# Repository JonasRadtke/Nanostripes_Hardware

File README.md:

# Nanostripes Hardware

## Nanostripes Led Modul

Dies ist das Led Modul für die Nanostripes Connectoren.
Der Connector sowie das LED Modul ist den Nanoleaf Lines nachempfunden. Auf dem Controller läuft das Reverse Engineered Nanoleaf Lines Protokoll.

## Nanostripes Connector

Dies ist der Connector für die Nanostripes Led Module.
Der Connector sowie das LED Modul ist den Nanoleaf Lines nachempfunden. Auf dem Controller läuft das Reverse Engineered Nanoleaf Lines Protokoll.

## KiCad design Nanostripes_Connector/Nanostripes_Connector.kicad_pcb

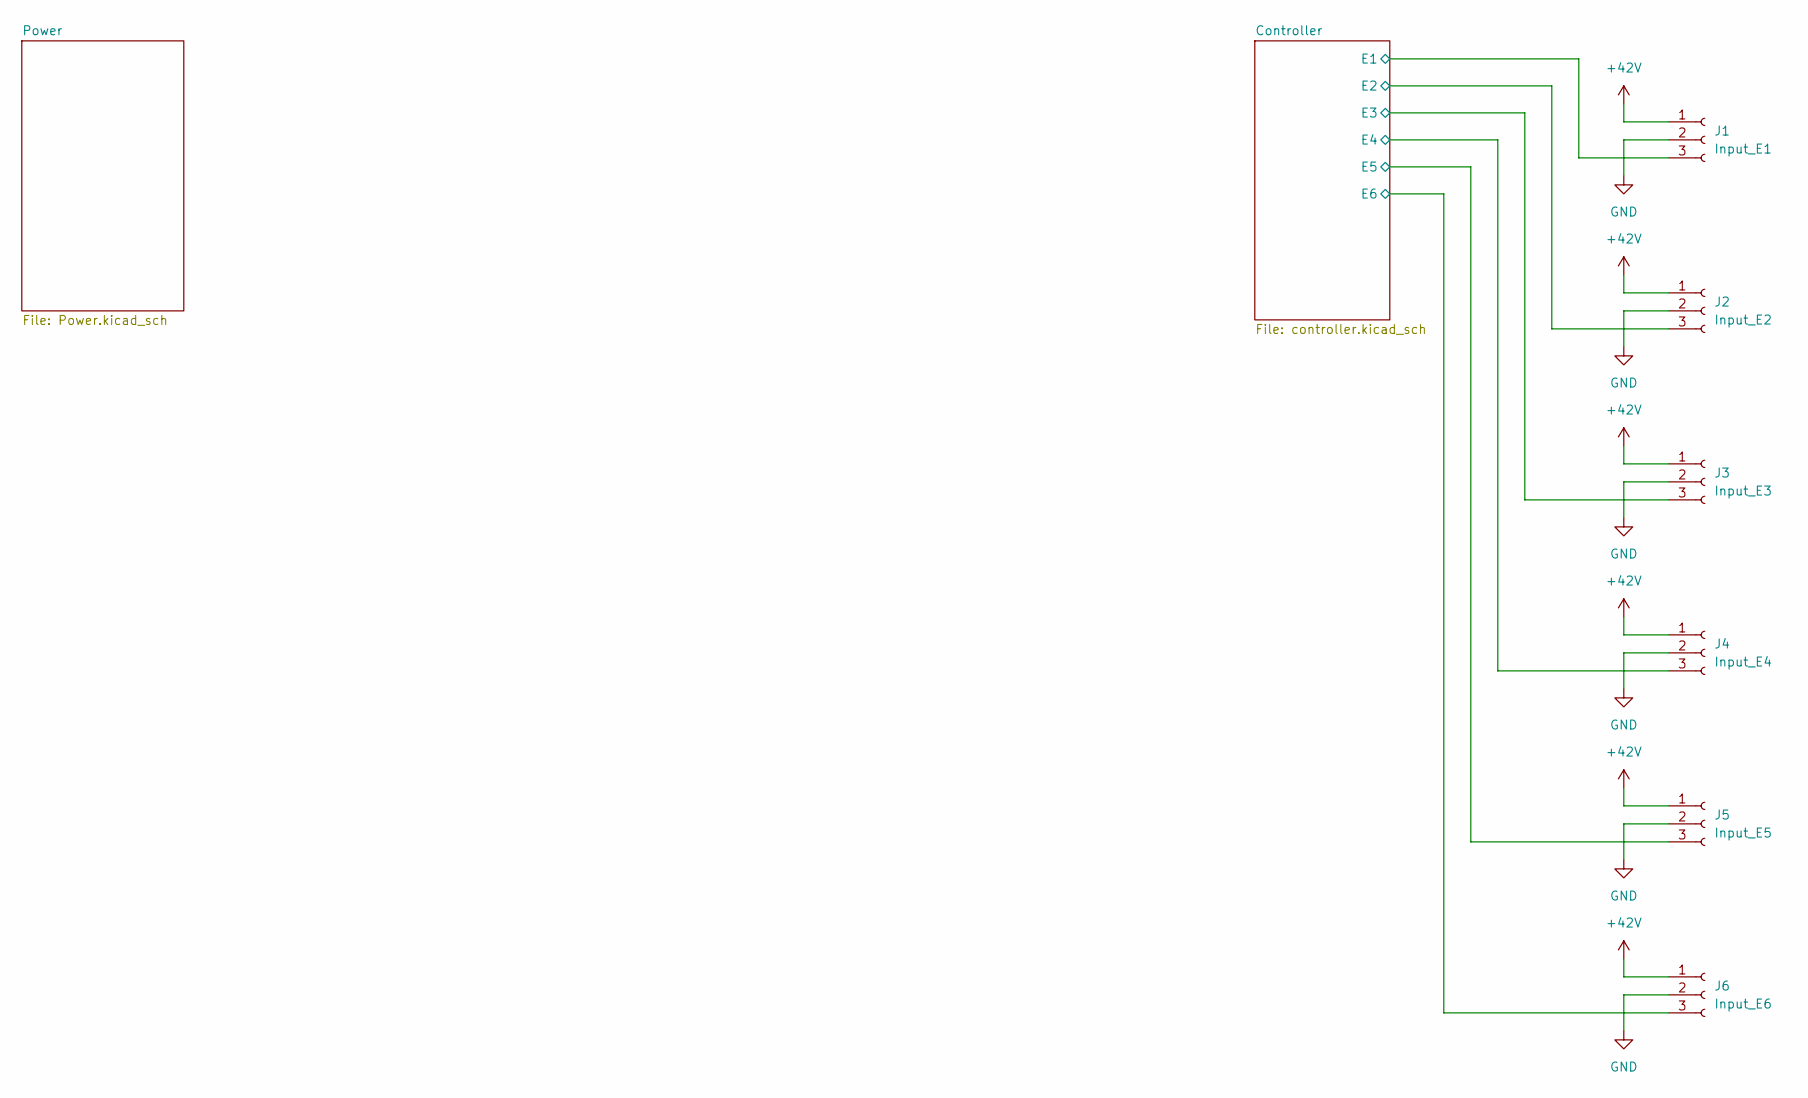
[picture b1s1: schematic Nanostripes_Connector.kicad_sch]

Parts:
J1: Input_E1; PinSocket_1x03_P2.54mm_Vertical
J2: Input_E2; PinSocket_1x03_P2.54mm_Vertical
J3: Input_E3; PinSocket_1x03_P2.54mm_Vertical
J4: Input_E4; PinSocket_1x03_P2.54mm_Vertical
J5: Input_E5; PinSocket_1x03_P2.54mm_Vertical
J6: Input_E6; PinSocket_1x03_P2.54mm_Vertical

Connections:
+42V: J1.1, J2.1, J3.1, J4.1, J5.1, J6.1; also elsewhere on the board
/Controller/E1: J1.3; also elsewhere on the board
/Controller/E2: J2.3; also elsewhere on the board
/Controller/E3: J3.3; also elsewhere on the board
/Controller/E4: J4.3; also elsewhere on the board
/Controller/E5: J5.3; also elsewhere on the board
/Controller/E6: J6.3; also elsewhere on the board
GND: J1.2, J2.2, J3.2, J4.2, J5.2, J6.2; also elsewhere on the board

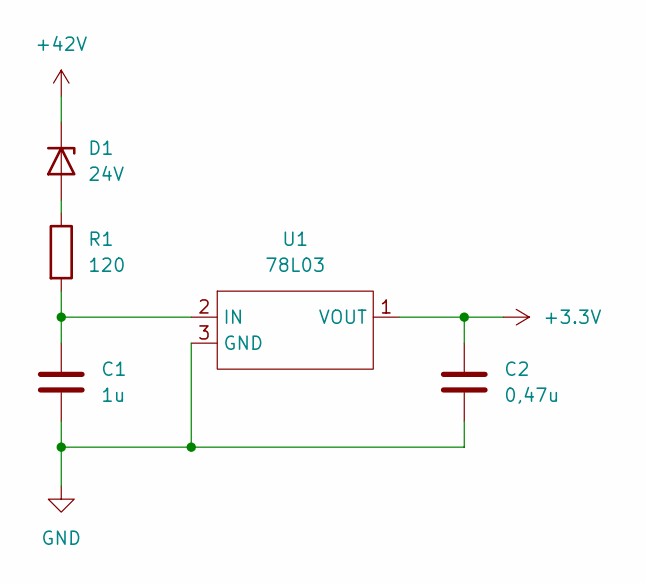
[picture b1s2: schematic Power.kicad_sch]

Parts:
C1: 1u; C_0805_2012Metric
C2: 0,47u; C_0805_2012Metric
D1: 24V; D_MiniMELF
R1: 120; R_0805_2012Metric
U1: 78L03; SOT-23-3

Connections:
+3.3V: C2.1, U1.1 (VOUT); also elsewhere on the board
+42V: D1.1 (K); also elsewhere on the board
GND: C1.2, C2.2, U1.3 (GND); also elsewhere on the board
unnamed: D1.2 (A), R1.1
unnamed: C1.1, R1.2, U1.2 (IN)

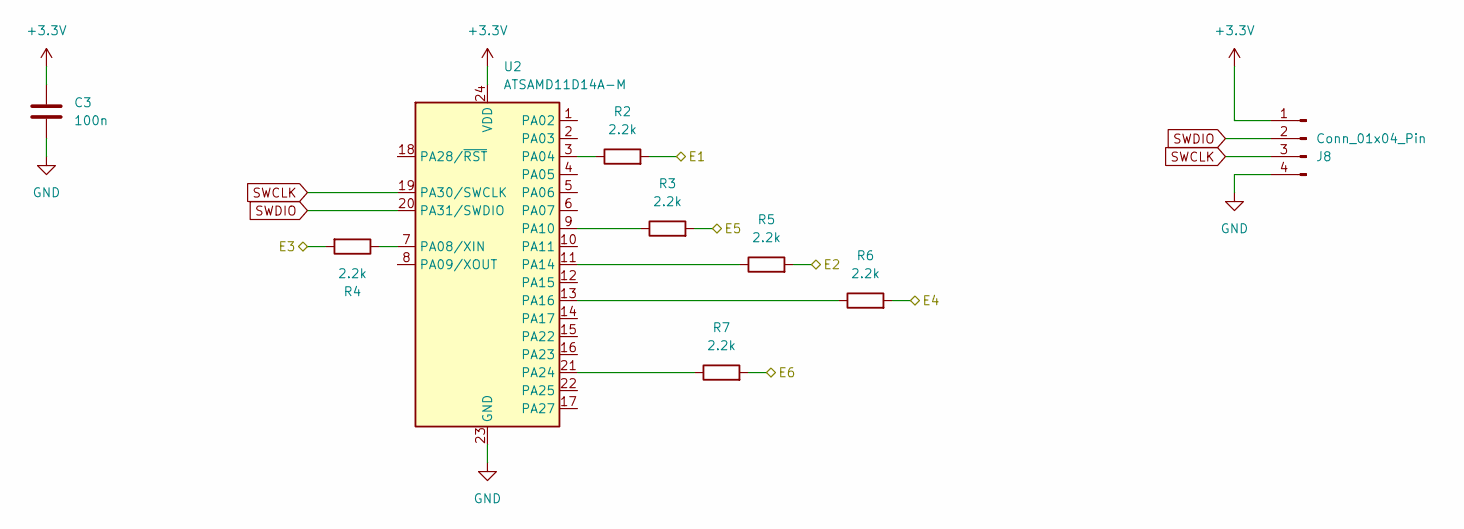
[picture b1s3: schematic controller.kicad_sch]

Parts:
C3: 100n; C_0805_2012Metric
J8: Conn_01x04_Pin; PinHeader_1x04_P2.54mm_Vertical
R2, R3, R4, R5, R6, R7: 2.2k; R_0805_2012Metric
U2: ATSAMD11D14A-M; QFN-24-1EP_4x4mm_P0.5mm_EP2.6x2.6mm

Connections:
+3.3V: C3.1, J8.1, U2.24 (VDD); also elsewhere on the board
/Controller/E1: R2.2; also elsewhere on the board
/Controller/E2: R5.2; also elsewhere on the board
/Controller/E3: R4.2; also elsewhere on the board
/Controller/E4: R6.2; also elsewhere on the board
/Controller/E5: R3.2; also elsewhere on the board
/Controller/E6: R7.2; also elsewhere on the board
GND: C3.2, J8.4, U2.23 (GND); also elsewhere on the board
unnamed: R2.1, U2.3 (PA04)
unnamed: R4.1, U2.7 (PA08/XIN)
unnamed: R3.1, U2.9 (PA10)
unnamed: R5.1, U2.11 (PA14)
unnamed: R6.1, U2.13 (PA16)
unnamed: R7.1, U2.21 (PA24)
SWCLK: J8.3, U2.19 (PA30/SWCLK)
SWDIO: J8.2, U2.20 (PA31/SWDIO)

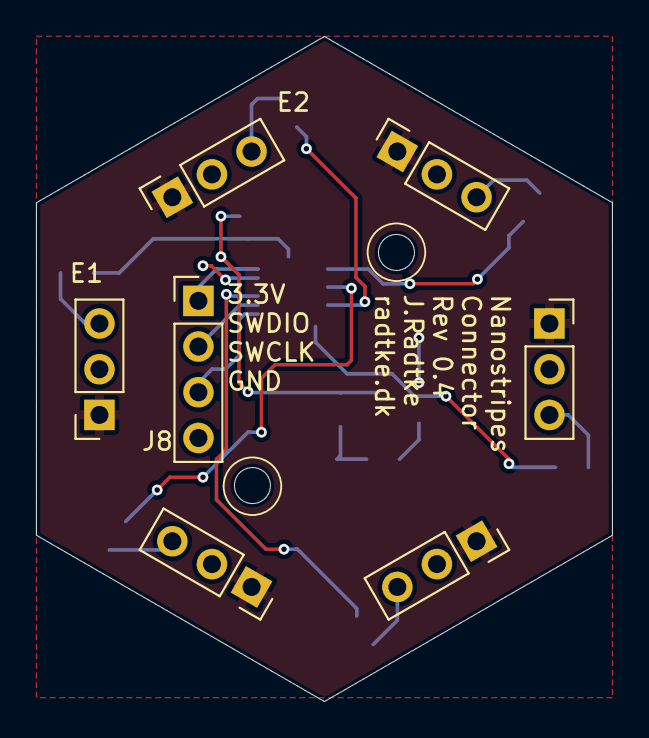
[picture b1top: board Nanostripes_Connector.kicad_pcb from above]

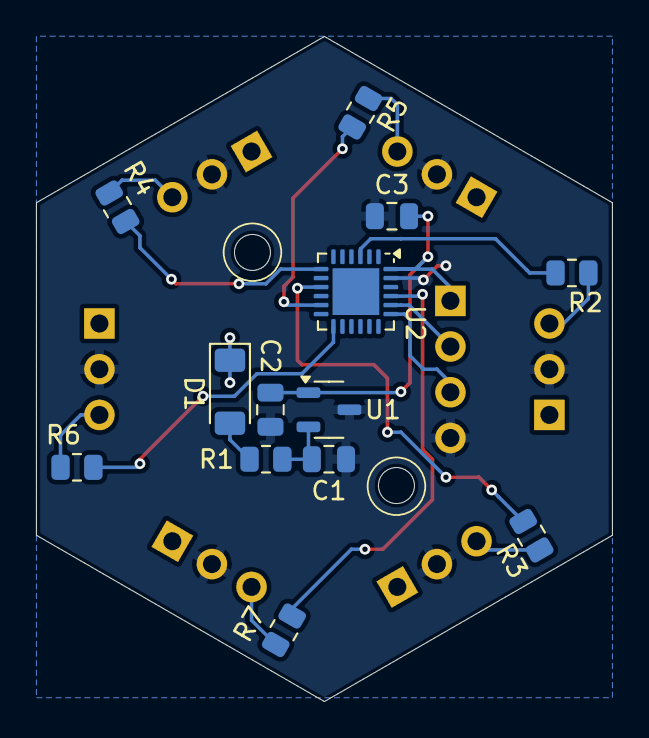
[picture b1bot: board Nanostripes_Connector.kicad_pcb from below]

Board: 2 copper layers, 32.0 x 37.0 mm, 20 parts (13 on the bottom side), 19 nets.

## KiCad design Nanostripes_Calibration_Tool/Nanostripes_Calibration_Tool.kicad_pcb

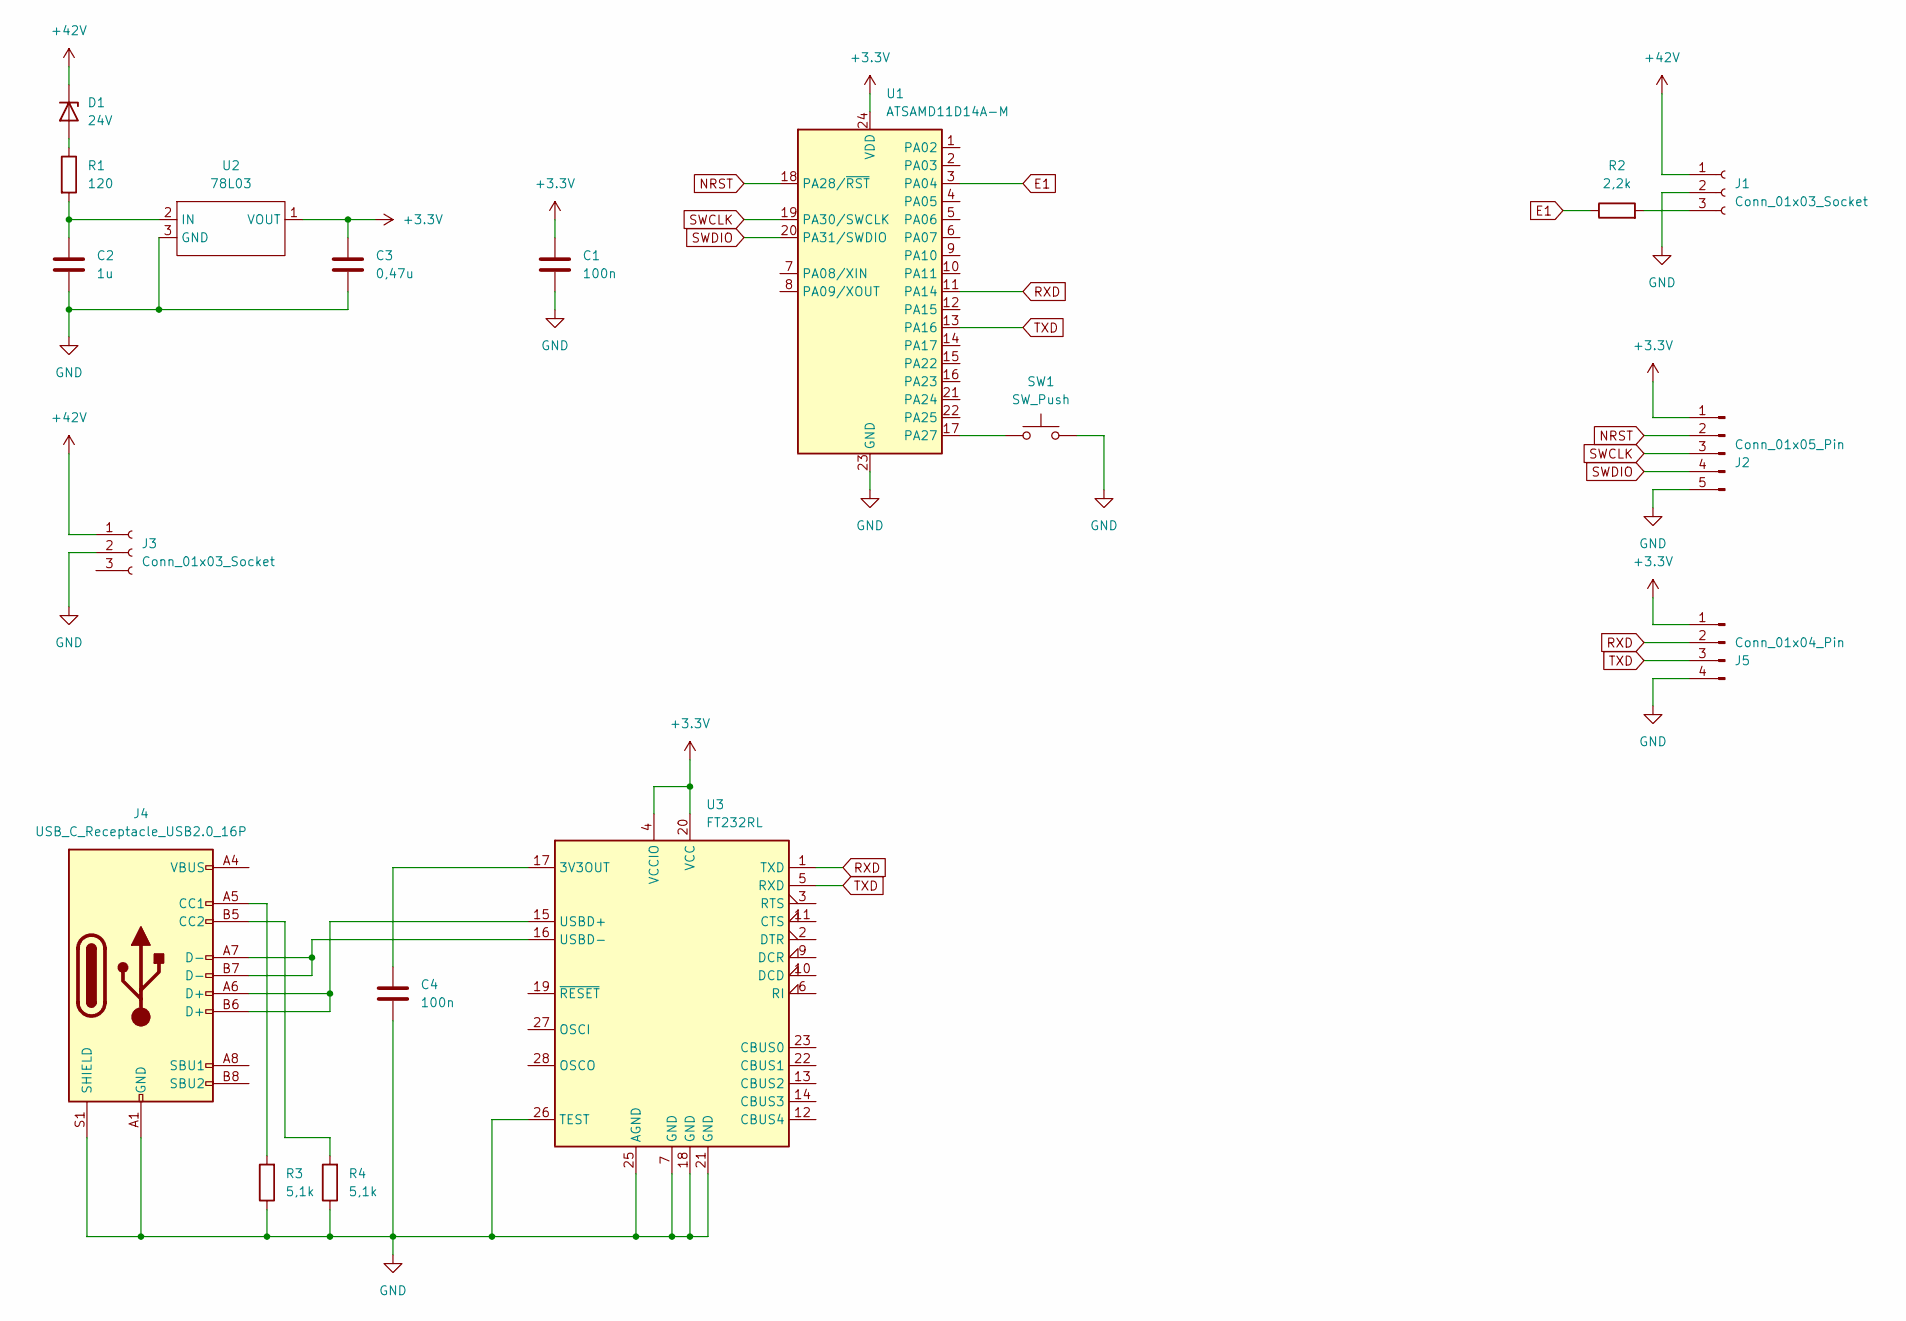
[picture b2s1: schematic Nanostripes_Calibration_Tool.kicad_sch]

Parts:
C1, C4: 100n; C_0805_2012Metric
C2: 1u; C_0805_2012Metric
C3: 0,47u; C_0805_2012Metric
D1: 24V; D_MiniMELF
J1, J3: Conn_01x03_Socket; PinSocket_1x03_P2.54mm_Vertical
J2: Conn_01x05_Pin; PinHeader_1x05_P2.54mm_Vertical
J4: USB_C_Receptacle_USB2.0_16P; TYPE-C-31-M-14
J5: Conn_01x04_Pin; PinHeader_1x04_P2.54mm_Vertical
R1: 120; R_0805_2012Metric
R2: 2,2k; R_0805_2012Metric
R3, R4: 5,1k; R_0805_2012Metric
SW1: SW_Push; SW_TH_Tactile_Omron_B3F-10xx
U1: ATSAMD11D14A-M; QFN-24-1EP_4x4mm_P0.5mm_EP2.6x2.6mm
U2: 78L03; SOT-23-3
U3: FT232RL; SSOP-28_5.3x10.2mm_P0.65mm

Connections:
+3.3V: C1.1, C3.1, J2.1, J5.1, U1.24 (VDD), U2.1 (VOUT), U3.4 (VCCIO), U3.20 (VCC)
+42V: D1.1 (K), J1.1, J3.1
E1: R2.1, U1.3 (PA04)
GND: C1.2, C2.2, C3.2, C4.2, J1.2, J2.5, J3.2, J4.A1 (GND), J4.A12 (GND), J4.B1 (GND), J4.B12 (GND), J4.S1 (SHIELD), J5.4, R3.1, R4.1, SW1.2, U1.23 (GND), U2.3 (GND), U3.7 (GND), U3.18 (GND), U3.21 (GND), U3.25 (AGND), U3.26 (TEST)
NRST: J2.2, U1.18 (PA28/~RST)
unnamed: D1.2 (A), R1.1
unnamed: J1.3, R2.2
unnamed: J4.A5 (CC1), R3.2
unnamed: J4.B5 (CC2), R4.2
unnamed: J4.A4 (VBUS), J4.A9 (VBUS), J4.B4 (VBUS), J4.B9 (VBUS)
unnamed: SW1.1, U1.17 (PA27)
unnamed: C2.1, R1.2, U2.2 (IN)
unnamed: C4.1, U3.17 (3V3OUT)
unnamed: J4.A6 (D+), J4.B6 (D+), U3.15 (USBD+)
unnamed: J4.A7 (D-), J4.B7 (D-), U3.16 (USBD-)
RXD: J5.2, U1.11 (PA14), U3.1 (TXD)
SWCLK: J2.3, U1.19 (PA30/SWCLK)
SWDIO: J2.4, U1.20 (PA31/SWDIO)
TXD: J5.3, U1.13 (PA16), U3.5 (RXD)

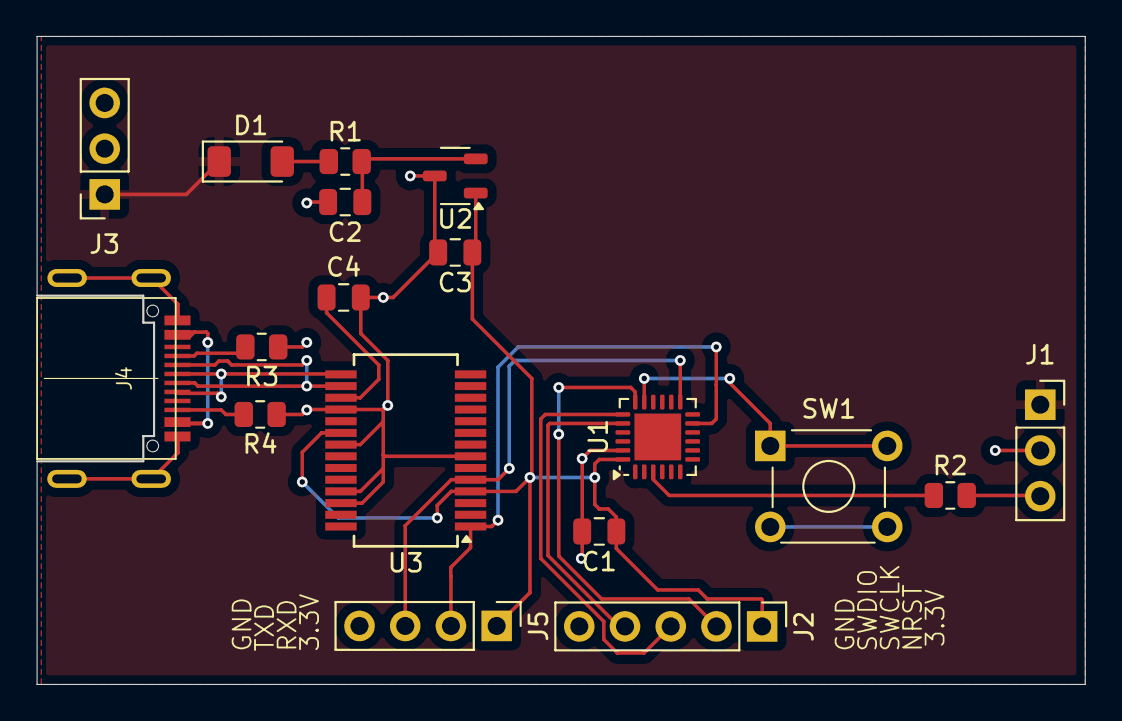
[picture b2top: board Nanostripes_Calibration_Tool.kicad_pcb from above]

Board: 2 copper layers, 58.2 x 36.0 mm, 18 parts (0 on the bottom side), 19 nets.

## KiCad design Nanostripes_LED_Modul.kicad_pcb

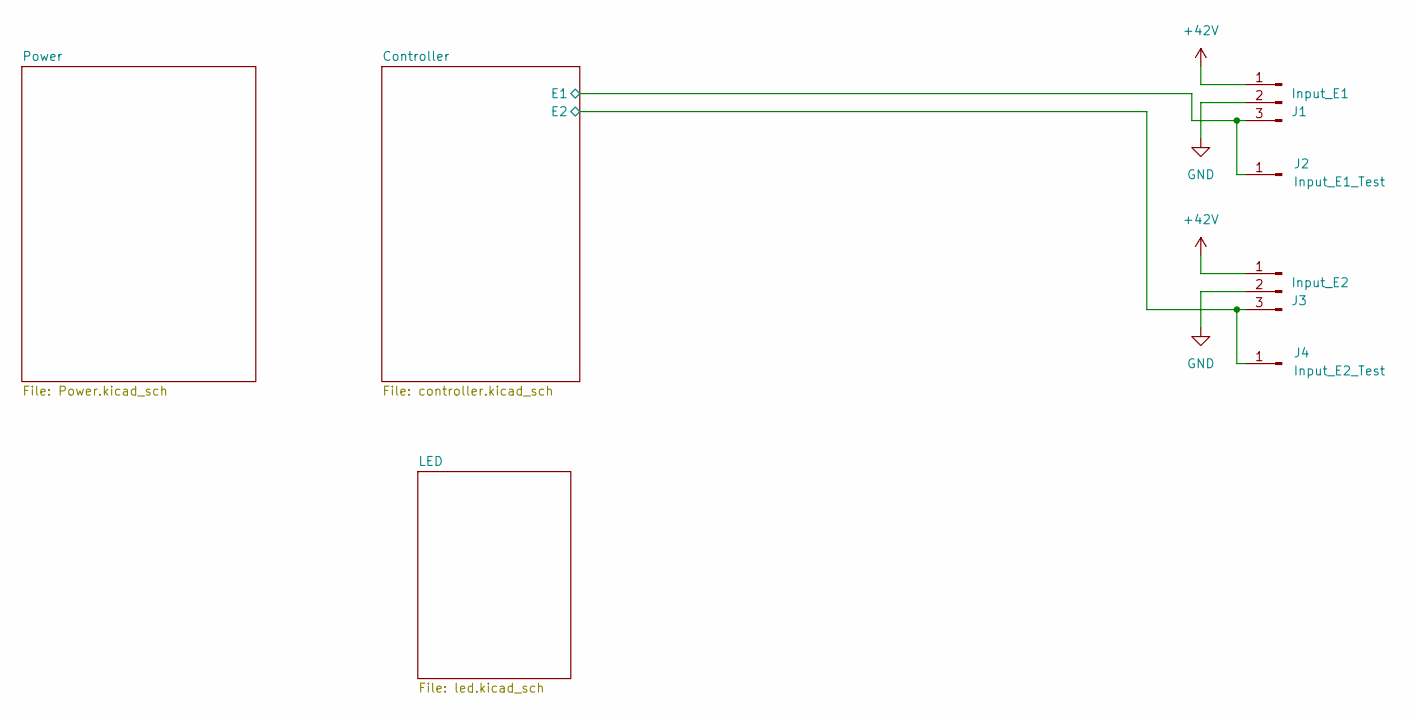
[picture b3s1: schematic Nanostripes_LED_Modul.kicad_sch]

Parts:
J1: Input_E1; PinHeader_1x03_P2.54mm_Vertical
J2: Input_E1_Test; PinHeader_1x01_P2.54mm_Vertical
J3: Input_E2; PinHeader_1x03_P2.54mm_Vertical
J4: Input_E2_Test; PinHeader_1x01_P2.54mm_Vertical

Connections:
+42V: J1.1, J3.1; also elsewhere on the board
/Controller/E1: J1.3, J2.1; also elsewhere on the board
/Controller/E2: J3.3, J4.1; also elsewhere on the board
GND: J1.2, J3.2; also elsewhere on the board

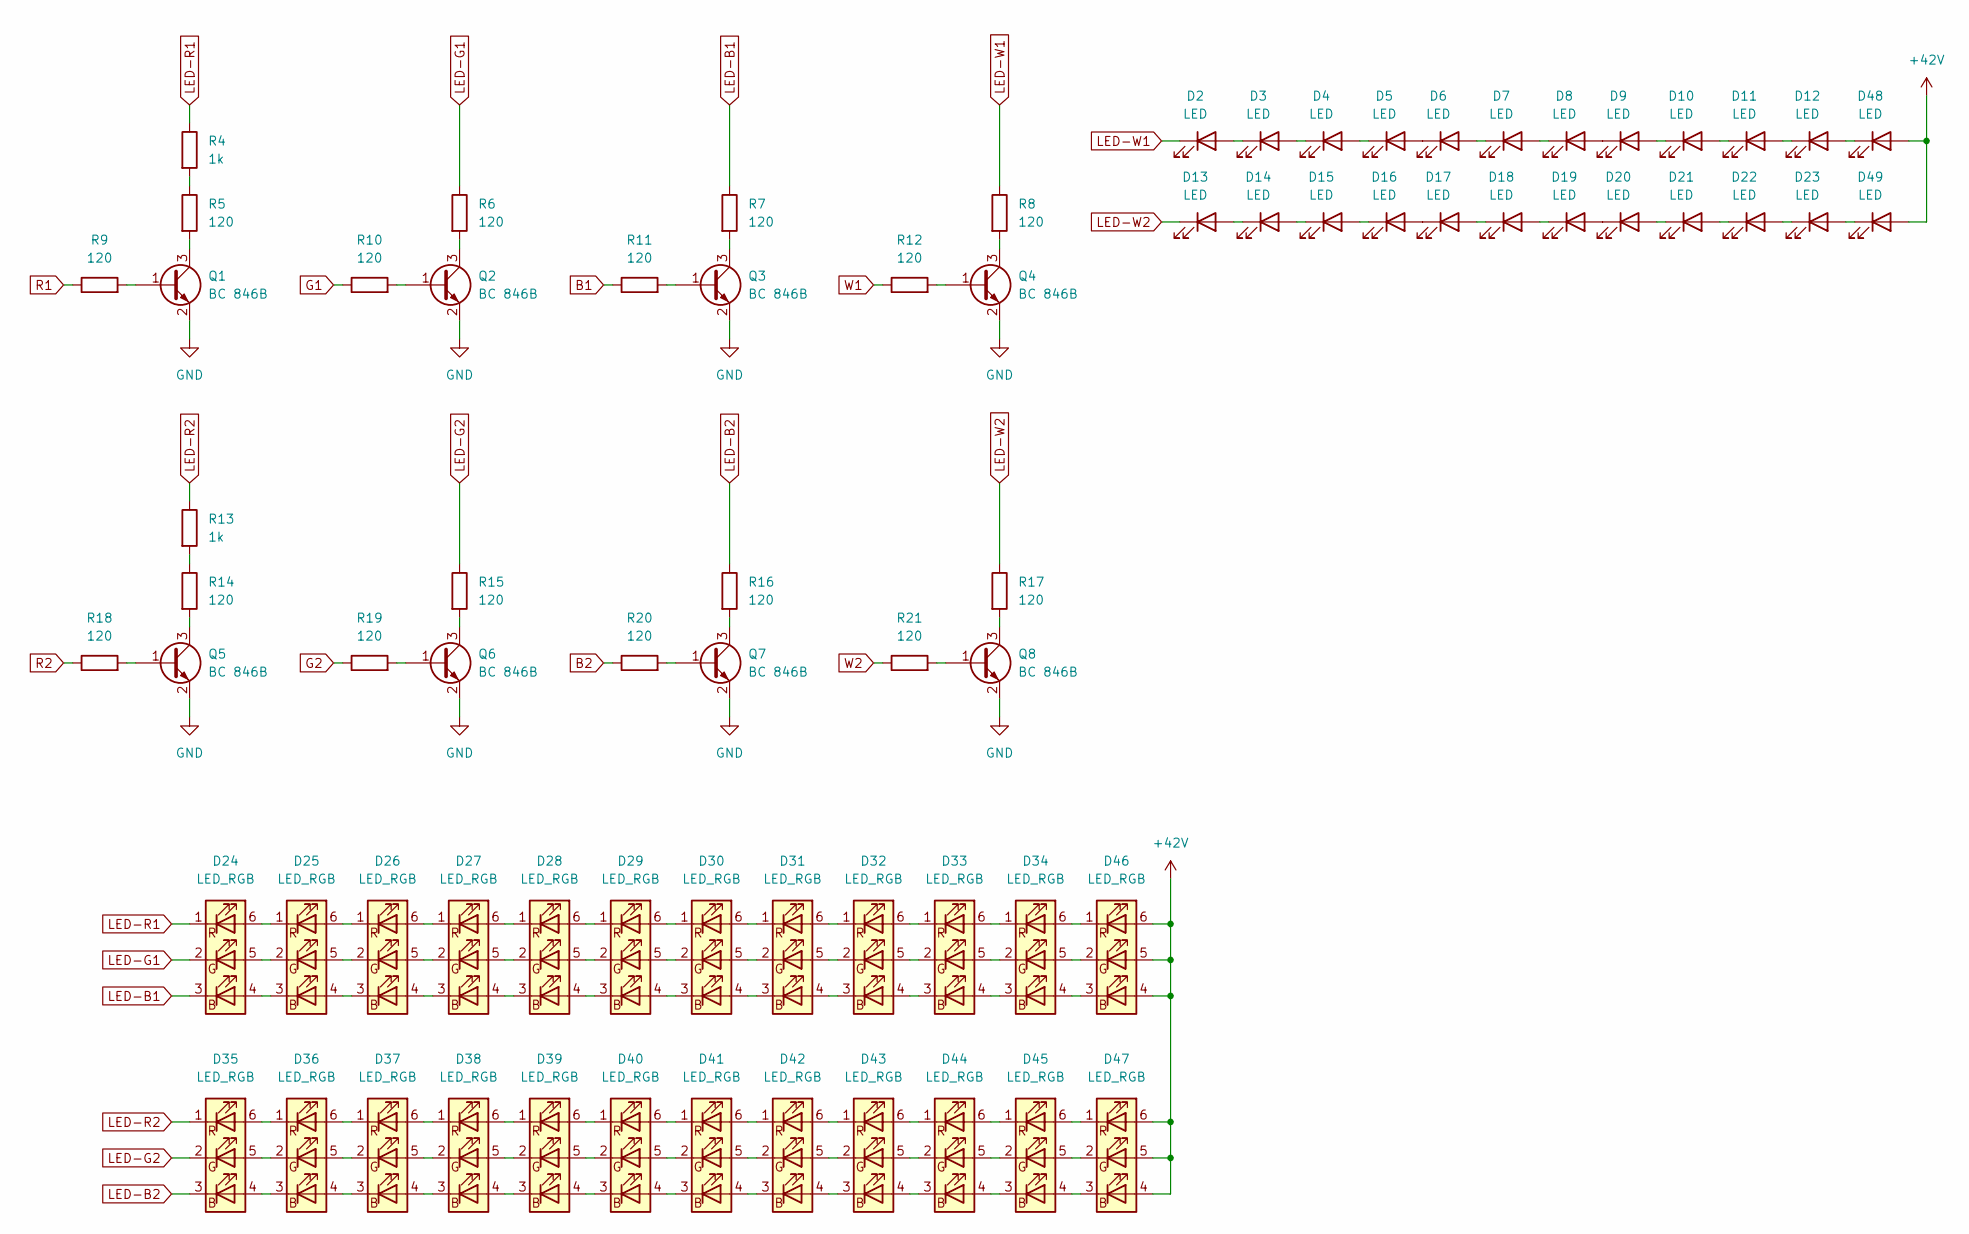
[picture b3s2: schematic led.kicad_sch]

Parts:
D2, D3, D4, D5, D6, D7, D8, D9, D10, D11, D12, D13, D14, D15, D16, D17, D18, D19, D20, D21, D22, D23, D48, D49: LED; LED_PLCC_2835
D24, D25, D26, D27, D28, D29, D30, D31, D32, D33, D34, D35, D36, D37, D38, D39, D40, D41, D42, D43, D44, D45, D46, D47: LED_RGB; LED_RGB_5050-6
Q1, Q2, Q3, Q4, Q5, Q6, Q7, Q8: BC 846B; TSOT-23
R4, R13: 1k; R_1206_3216Metric
R5, R6, R7, R8, R9, R10, R11, R12, R14, R15, R16, R17, R18, R19, R20, R21: 120; R_0805_2012Metric

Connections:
+42V: D46.4 (BA), D46.5 (GA), D46.6 (RA), D47.4 (BA), D47.5 (GA), D47.6 (RA), D48.2 (A), D49.2 (A); also elsewhere on the board
B1: R11.1; also elsewhere on the board
B2: R20.1; also elsewhere on the board
G1: R10.1; also elsewhere on the board
G2: R19.1; also elsewhere on the board
GND: Q1.2 (E), Q2.2 (E), Q3.2 (E), Q4.2 (E), Q5.2 (E), Q6.2 (E), Q7.2 (E), Q8.2 (E); also elsewhere on the board
LED-B1: D24.3 (BK), R7.1
LED-B2: D35.3 (BK), R16.1
LED-G1: D24.2 (GK), R6.1
LED-G2: D35.2 (GK), R15.1
LED-R1: D24.1 (RK), R4.1
LED-R2: D35.1 (RK), R13.1
LED-W1: D2.1 (K), R8.1
LED-W2: D13.1 (K), R17.1
unnamed: D2.2 (A), D3.1 (K)
unnamed: D3.2 (A), D4.1 (K)
unnamed: D4.2 (A), D5.1 (K)
unnamed: D5.2 (A), D6.1 (K)
unnamed: D6.2 (A), D7.1 (K)
unnamed: D7.2 (A), D8.1 (K)
unnamed: D8.2 (A), D9.1 (K)
unnamed: D10.2 (A), D11.1 (K)
unnamed: D9.2 (A), D10.1 (K)
unnamed: D11.2 (A), D12.1 (K)
unnamed: D12.2 (A), D48.1 (K)
unnamed: D13.2 (A), D14.1 (K)
unnamed: D14.2 (A), D15.1 (K)
unnamed: D15.2 (A), D16.1 (K)
unnamed: D16.2 (A), D17.1 (K)
unnamed: D17.2 (A), D18.1 (K)
unnamed: D18.2 (A), D19.1 (K)
unnamed: D19.2 (A), D20.1 (K)
unnamed: D20.2 (A), D21.1 (K)
unnamed: D21.2 (A), D22.1 (K)
unnamed: D22.2 (A), D23.1 (K)
unnamed: D23.2 (A), D49.1 (K)
unnamed: D24.4 (BA), D25.3 (BK)
unnamed: D24.5 (GA), D25.2 (GK)
unnamed: D24.6 (RA), D25.1 (RK)
unnamed: D25.4 (BA), D26.3 (BK)
unnamed: D25.5 (GA), D26.2 (GK)
unnamed: D25.6 (RA), D26.1 (RK)
unnamed: D26.4 (BA), D27.3 (BK)
unnamed: D26.5 (GA), D27.2 (GK)
unnamed: D26.6 (RA), D27.1 (RK)
unnamed: D27.4 (BA), D28.3 (BK)
unnamed: D27.5 (GA), D28.2 (GK)
unnamed: D27.6 (RA), D28.1 (RK)
unnamed: D28.4 (BA), D29.3 (BK)
unnamed: D28.5 (GA), D29.2 (GK)
unnamed: D28.6 (RA), D29.1 (RK)
unnamed: D29.4 (BA), D30.3 (BK)
unnamed: D29.5 (GA), D30.2 (GK)
unnamed: D29.6 (RA), D30.1 (RK)
unnamed: D30.4 (BA), D31.3 (BK)
unnamed: D30.5 (GA), D31.2 (GK)
unnamed: D30.6 (RA), D31.1 (RK)
unnamed: D31.4 (BA), D32.3 (BK)
unnamed: D31.5 (GA), D32.2 (GK)
unnamed: D31.6 (RA), D32.1 (RK)
unnamed: D32.4 (BA), D33.3 (BK)
unnamed: D32.5 (GA), D33.2 (GK)
unnamed: D32.6 (RA), D33.1 (RK)
unnamed: D33.4 (BA), D34.3 (BK)
unnamed: D33.5 (GA), D34.2 (GK)
unnamed: D33.6 (RA), D34.1 (RK)
unnamed: D34.4 (BA), D46.3 (BK)
unnamed: D34.5 (GA), D46.2 (GK)
unnamed: D34.6 (RA), D46.1 (RK)
unnamed: D35.4 (BA), D36.3 (BK)
unnamed: D35.5 (GA), D36.2 (GK)
unnamed: D35.6 (RA), D36.1 (RK)
unnamed: D36.4 (BA), D37.3 (BK)
unnamed: D36.5 (GA), D37.2 (GK)
unnamed: D36.6 (RA), D37.1 (RK)
unnamed: D37.4 (BA), D38.3 (BK)
unnamed: D37.5 (GA), D38.2 (GK)
unnamed: D37.6 (RA), D38.1 (RK)
unnamed: D38.4 (BA), D39.3 (BK)
unnamed: D38.5 (GA), D39.2 (GK)
unnamed: D38.6 (RA), D39.1 (RK)
unnamed: D39.4 (BA), D40.3 (BK)
unnamed: D39.5 (GA), D40.2 (GK)
unnamed: D39.6 (RA), D40.1 (RK)
unnamed: D40.4 (BA), D41.3 (BK)
unnamed: D40.5 (GA), D41.2 (GK)
unnamed: D40.6 (RA), D41.1 (RK)
unnamed: D41.4 (BA), D42.3 (BK)
unnamed: D41.5 (GA), D42.2 (GK)
unnamed: D41.6 (RA), D42.1 (RK)
unnamed: D42.4 (BA), D43.3 (BK)
unnamed: D42.5 (GA), D43.2 (GK)
unnamed: D42.6 (RA), D43.1 (RK)
unnamed: D43.4 (BA), D44.3 (BK)
unnamed: D43.5 (GA), D44.2 (GK)
unnamed: D43.6 (RA), D44.1 (RK)
unnamed: D44.4 (BA), D45.3 (BK)
unnamed: D44.5 (GA), D45.2 (GK)
unnamed: D44.6 (RA), D45.1 (RK)
unnamed: D45.4 (BA), D47.3 (BK)
unnamed: D45.5 (GA), D47.2 (GK)
unnamed: D45.6 (RA), D47.1 (RK)
unnamed: Q1.1 (B), R9.2
unnamed: Q1.3 (C), R5.2
unnamed: Q2.1 (B), R10.2
unnamed: Q2.3 (C), R6.2
unnamed: Q3.1 (B), R11.2
unnamed: Q3.3 (C), R7.2
unnamed: Q4.1 (B), R12.2
unnamed: Q4.3 (C), R8.2
unnamed: Q5.1 (B), R18.2
unnamed: Q5.3 (C), R14.2
unnamed: Q6.1 (B), R19.2
unnamed: Q6.3 (C), R15.2
unnamed: Q7.1 (B), R20.2
unnamed: Q7.3 (C), R16.2
unnamed: Q8.1 (B), R21.2
unnamed: Q8.3 (C), R17.2
unnamed: R4.2, R5.1
unnamed: R13.2, R14.1
R1: R9.1; also elsewhere on the board
R2: R18.1; also elsewhere on the board
W1: R12.1; also elsewhere on the board
W2: R21.1; also elsewhere on the board

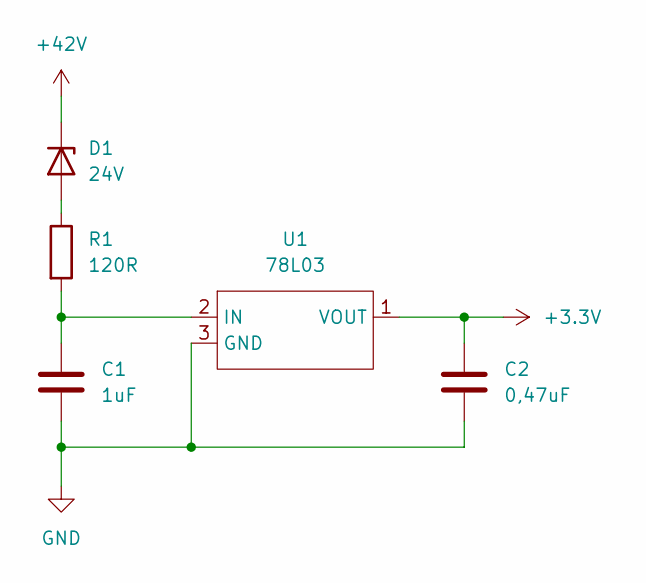
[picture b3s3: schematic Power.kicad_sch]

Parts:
C1: 1uF; C_0805_2012Metric
C2: 0,47uF; C_0805_2012Metric
D1: 24V; D_MiniMELF
R1: 120R; R_0805_2012Metric
U1: 78L03; SOT-23-3

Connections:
+3.3V: C2.1, U1.1 (VOUT); also elsewhere on the board
+42V: D1.1 (K); also elsewhere on the board
GND: C1.2, C2.2, U1.3 (GND); also elsewhere on the board
unnamed: D1.2 (A), R1.1
unnamed: C1.1, R1.2, U1.2 (IN)

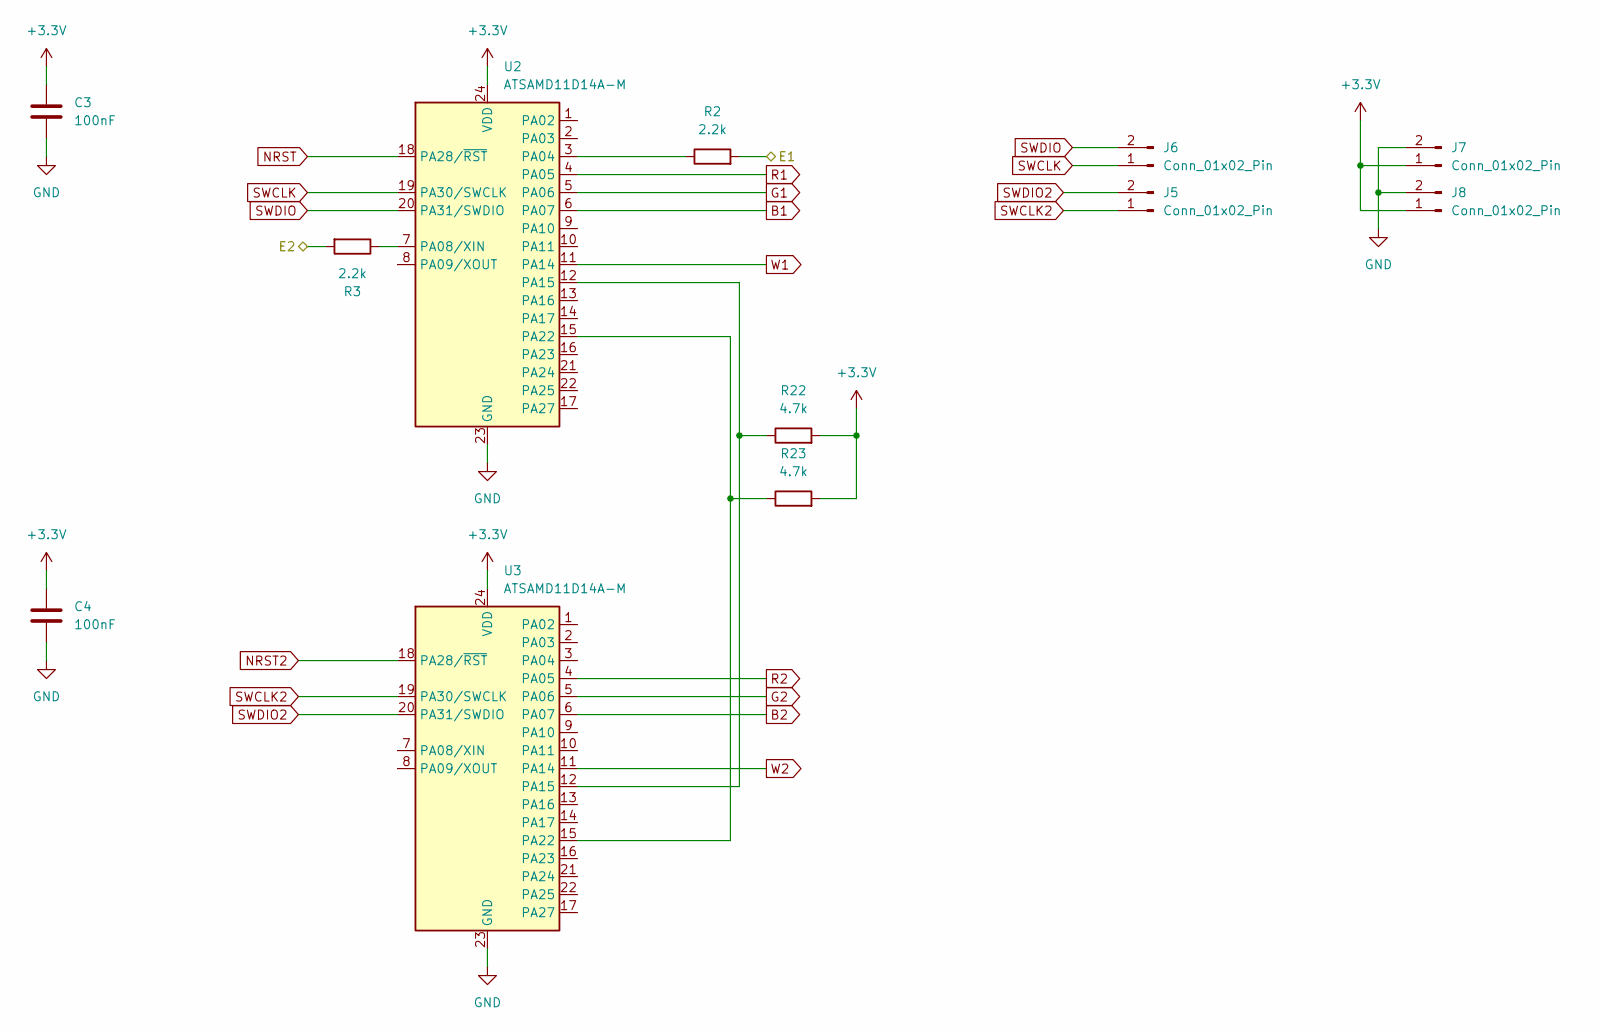
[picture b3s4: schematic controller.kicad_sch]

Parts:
C3, C4: 100nF; C_0805_2012Metric
J5, J6, J7, J8: Conn_01x02_Pin; PinHeader_1x02_P2.54mm_Vertical
R2, R3: 2.2k; R_0805_2012Metric
R22, R23: 4.7k; R_0805_2012Metric
U2, U3: ATSAMD11D14A-M; QFN-24-1EP_4x4mm_P0.5mm_EP2.6x2.6mm

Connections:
+3.3V: C3.1, C4.1, J7.1, J8.1, R22.2, R23.2, U2.24 (VDD), U3.24 (VDD); also elsewhere on the board
/Controller/E1: R2.2; also elsewhere on the board
/Controller/E2: R3.2; also elsewhere on the board
B1: U2.6 (PA07); also elsewhere on the board
B2: U3.6 (PA07); also elsewhere on the board
G1: U2.5 (PA06); also elsewhere on the board
G2: U3.5 (PA06); also elsewhere on the board
GND: C3.2, C4.2, J7.2, J8.2, U2.23 (GND), U3.23 (GND); also elsewhere on the board
NRST: U2.18 (PA28/~RST)
NRST2: U3.18 (PA28/~RST)
unnamed: R2.1, U2.3 (PA04)
unnamed: R3.1, U2.7 (PA08/XIN)
unnamed: R22.1, U2.12 (PA15), U3.12 (PA15)
unnamed: R23.1, U2.15 (PA22), U3.15 (PA22)
R1: U2.4 (PA05); also elsewhere on the board
R2: U3.4 (PA05); also elsewhere on the board
SWCLK: J6.1, U2.19 (PA30/SWCLK)
SWCLK2: J5.1, U3.19 (PA30/SWCLK)
SWDIO: J6.2, U2.20 (PA31/SWDIO)
SWDIO2: J5.2, U3.20 (PA31/SWDIO)
W1: U2.11 (PA14); also elsewhere on the board
W2: U3.11 (PA14); also elsewhere on the board

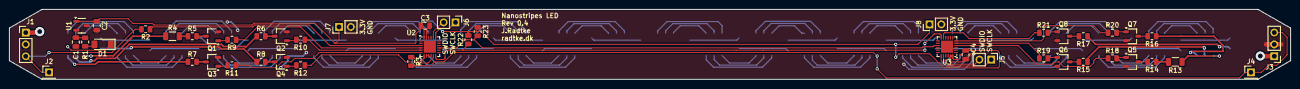
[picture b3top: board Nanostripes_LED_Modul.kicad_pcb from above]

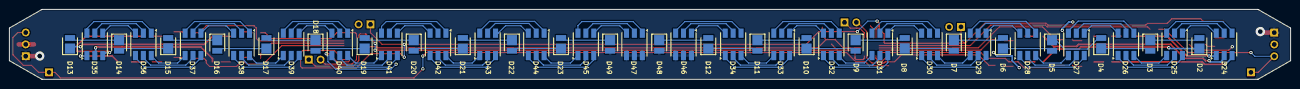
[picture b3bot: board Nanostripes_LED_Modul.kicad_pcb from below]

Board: 2 copper layers, 275.0 x 15.0 mm, 95 parts (48 on the bottom side), 137 nets.
